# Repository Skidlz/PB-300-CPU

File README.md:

# PB-300-CPU
A new replacement CPU for the Roland PB-300 drum machine

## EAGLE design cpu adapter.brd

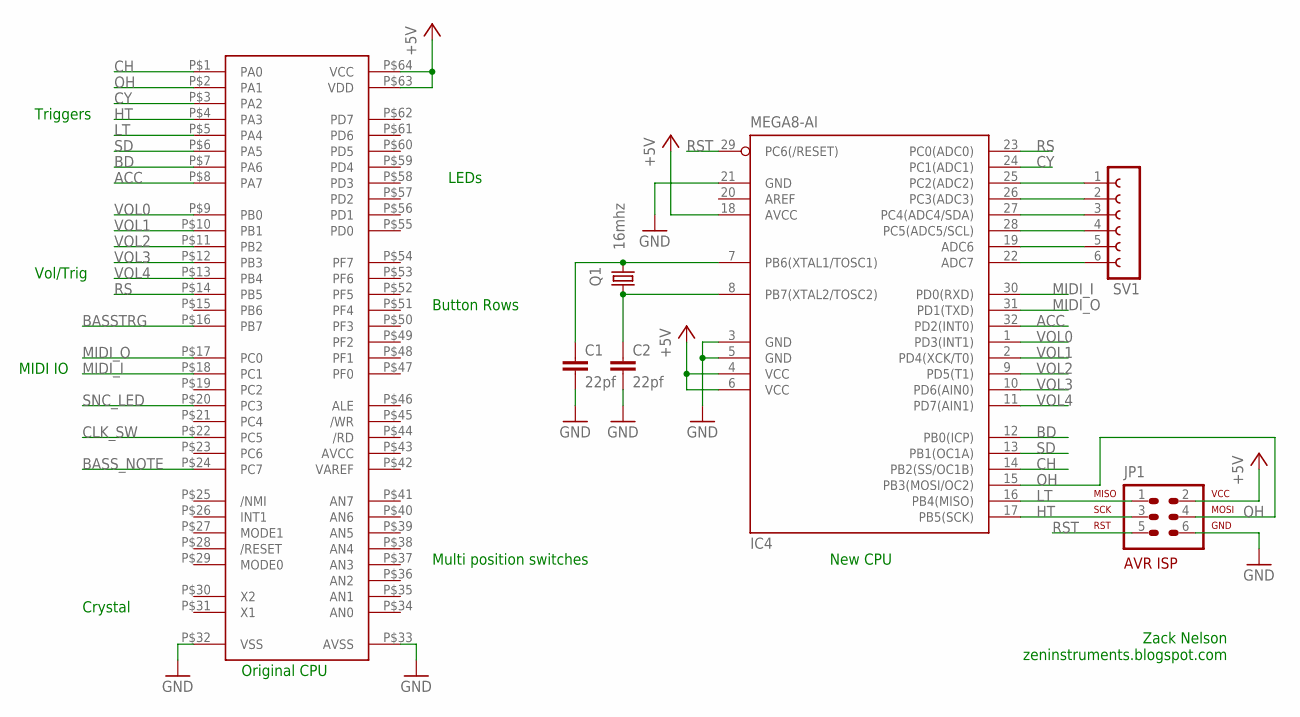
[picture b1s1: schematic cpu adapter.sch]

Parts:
C1, C2: 22pf; C025-024X044
IC1: D7811G; 64STAG
IC4: MEGA8-AI; TQFP32-08
JP1: AVR-ISP-6
Q1: 16mhz; HC18U-V
SV1: FE06-1; FE06

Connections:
+5V: IC1.P$63 (VDD), IC1.P$64 (VCC), IC4.4 (VCC), IC4.6 (VCC), IC4.18 (AVCC), JP1.2
ACC: IC1.P$8 (PA7), IC4.32 (PD2(INT0))
BASSTRG: IC1.P$16 (PB7)
BASS_NOTE: IC1.P$24 (PC7)
BD: IC1.P$7 (PA6), IC4.12 (PB0(ICP))
CH: IC1.P$1 (PA0), IC4.14 (PB2(SS/OC1B))
CLK_SW: IC1.P$22 (PC5)
CY: IC1.P$3 (PA2), IC4.24 (PC1(ADC1))
GND: C1.2, C2.2, IC1.P$32 (VSS), IC1.P$33 (AVSS), IC4.3 (GND), IC4.5 (GND), IC4.21 (GND), JP1.6
HT: IC1.P$4 (PA3), IC4.17 (PB5(SCK)), JP1.3
LB: IC4.27 (PC4(ADC4/SDA)), SV1.3
LT: IC1.P$5 (PA4), IC4.16 (PB4(MISO)), JP1.1
MB: IC4.19 (ADC6), SV1.5
MIDI_I: IC1.P$18 (PC1), IC4.30 (PD0(RXD))
MIDI_O: IC1.P$17 (PC0), IC4.31 (PD1(TXD))
unnamed: IC4.22 (ADC7), SV1.6
unnamed: C1.1, IC4.7 (PB6(XTAL1/TOSC1)), Q1.2
unnamed: C2.1, IC4.8 (PB7(XTAL2/TOSC2)), Q1.1
OH: IC1.P$2 (PA1), IC4.15 (PB3(MOSI/OC2)), JP1.4
RB: IC4.28 (PC5(ADC5/SCL)), SV1.4
RS: IC1.P$14 (PB5), IC4.23 (PC0(ADC0))
RST: IC4.29 (PC6(/RESET)), JP1.5
SD: IC1.P$6 (PA5), IC4.13 (PB1(OC1A))
SNC_LED: IC1.P$20 (PC3)
VOL0: IC1.P$9 (PB0), IC4.1 (PD3(INT1))
VOL1: IC1.P$10 (PB1), IC4.2 (PD4(XCK/T0))
VOL2: IC1.P$11 (PB2), IC4.9 (PD5(T1))
VOL3: IC1.P$12 (PB3), IC4.10 (PD6(AIN0))
VOL4: IC1.P$13 (PB4), IC4.11 (PD7(AIN1))
YA: IC4.25 (PC2(ADC2)), SV1.1
YB: IC4.26 (PC3(ADC3)), SV1.2

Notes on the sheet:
Multi position switches
Button Rows
MIDI IO
Triggers
Vol/Trig
LEDs
Crystal
Original CPU
New CPU
Zack Nelson zeninstruments.blogspot.com

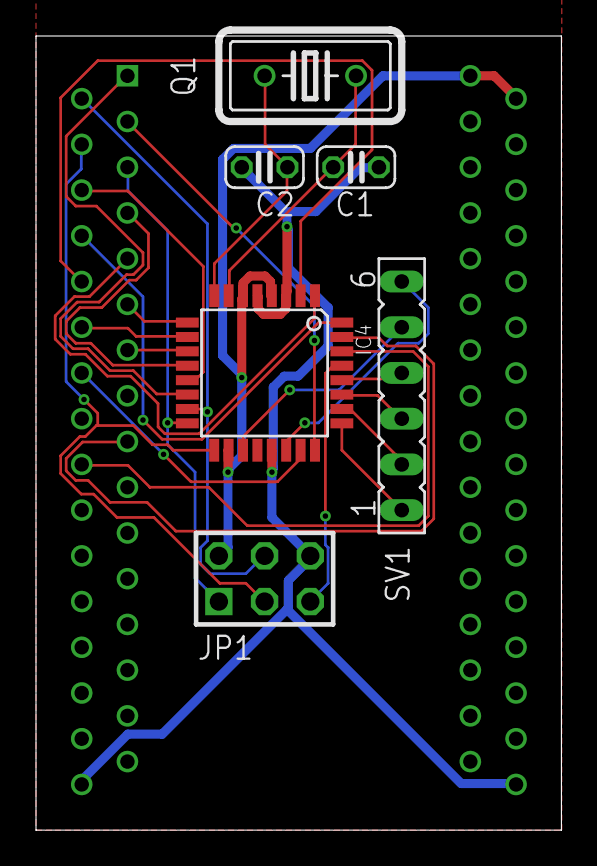
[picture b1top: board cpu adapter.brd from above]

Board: 2 copper layers, 29.2 x 44.1 mm, 7 parts (0 on the bottom side), 27 nets.

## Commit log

2020-12-29 Adding Schematic
